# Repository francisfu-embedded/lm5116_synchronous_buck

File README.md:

# lm5116_synchronous_buck
a 72W synchronous buck converter based on TI LM5116

- Features:
Input voltage range from 15 - 50V
Output Voltage: 12V    +- 2.5%
Output Current: Max 6A. Shuts off after reaching the limit
Max efficiency 96% at full load

- Notes:
The inductor of this buck converter circuit is changed from a 22u vishay smd inductor to a 97u toroidal inductor due to excessive inductor heating at no load.
The suspected reason is the inductor current spiking at light load DCM. 
Replacing with higher inductance solves the issue in the design as it decreases the output load "boundary" to CCM
Further investigations on this behaviour still needed!

- Remaining issues:
1. The current design has bad "acoustics". Inductor buzzing is audible. It is normal to have a buzzing noise in a switching converter prototype but it's still not
desirable. Further investigations needed on how to reduce this audible noise in a mature product.

2. After loading the converter and then returning back to no load, the buck converter still draws around 2.1W standby power - which is not seen when the circuit is first
powered up. Further inverstigations needed on this high standby power. It may have to do with the ic itself not in "standby" mode and / or the inductor current spiking
at no load

- Potential applications:
This project is a prototype design using TI's LM5116 and may open up more design ideas involving this chip. For instance, a fan driver or an AA battery charger.
The feedback voltage can be made programmable easily by attaching a filtered-pwm / DAC / pull-down resistors to the feedback pin, thus enabling voltage programming
or even current regulation using an external control loop (e.g. using an MCU). This control scheme is suitable for chargers and variable power supply. Related project 
maybe added to the github in the future.

- Thanks:
Big shout-outs to TI's engineers for their great documentation of the IC and their reference designs

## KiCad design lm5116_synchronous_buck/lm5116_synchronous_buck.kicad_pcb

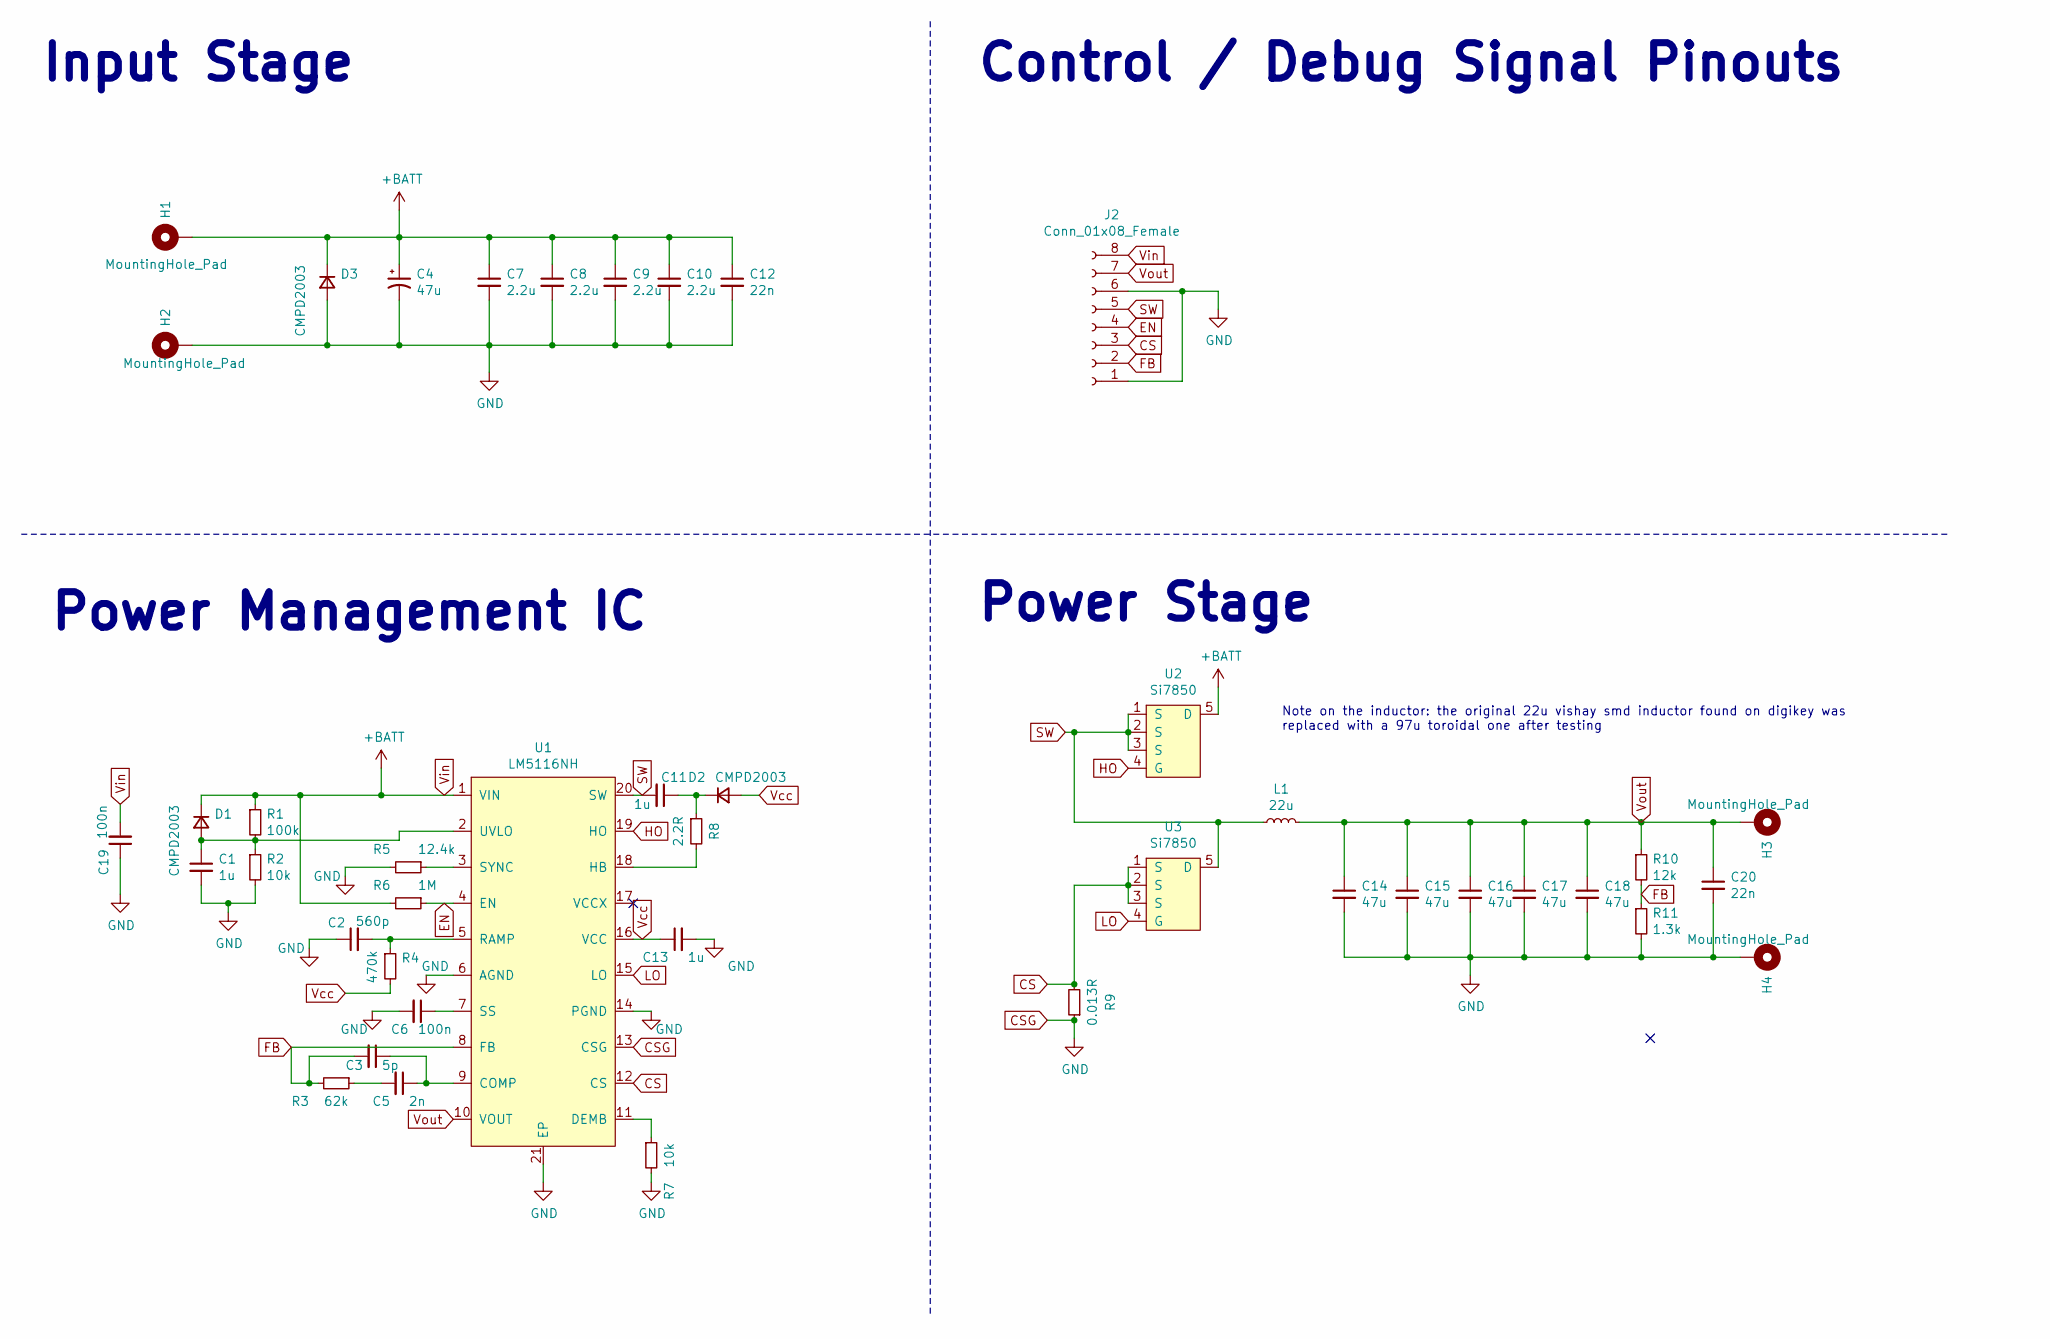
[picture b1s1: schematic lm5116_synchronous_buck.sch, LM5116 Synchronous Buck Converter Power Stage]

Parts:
C1, C11, C13: 1u; C_0603_1608Metric; LCSC Part # C90540
C2: 560p; C_0603_1608Metric; LCSC Part # C1627
C3: 5p; C_0603_1608Metric; LCSC Part # C1669
C4: 47u; C_Elec_8x10.2; LCSC Part # C336483
C5: 2n; C_0603_1608Metric; LCSC Part # C1604
C6, C19: 100n; C_0603_1608Metric; LCSC Part # C83054
C7, C8, C9, C10: 2.2u; C_1206_3216Metric; LCSC Part # C39619
C12, C20: 22n; C_0603_1608Metric; LCSC Part # C1697
C14, C15, C16, C17, C18: 47u; C_1206_3216Metric; LCSC Part # C30300
D1, D2, D3: CMPD2003; D_SOT-23_ANK
H1, H2, H3, H4: MountingHole_Pad; MountingHole_4.5mm_Pad_Via
J2: Conn_01x08_Female; PinHeader_1x08_P2.54mm_Vertical
L1: 22u; L_12x12mm_H6mm
R1: 100k; R_0603_1608Metric; LCSC Part # C25803
R2, R7: 10k; R_0603_1608Metric; LCSC Part # C269701
R3: 62k; R_0603_1608Metric; LCSC Part # C23221
R4: 470k; R_0603_1608Metric; LCSC Part # C25599
R5: 12.4k; R_0603_1608Metric; LCSC Part # C22865
R6: 1M; R_0603_1608Metric; LCSC Part # C22935
R8: 2.2R; R_0805_2012Metric
R9: 0.013R; R_1206_3216Metric; LCSC Part # C201279
R10: 12k; R_0603_1608Metric; LCSC Part # C269442
R11: 1.3k; R_0603_1608Metric; LCSC Part # C22767
U1: LM5116NH; HTSSOP-20-1EP_4.4x6.5mm_P0.65mm_EP3.4x6.5mm; LCSC Part # C13755
U2, U3: Si7850; PowerPAK_SO-8_Single

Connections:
CS: J2.3, R9.2, U1.12 (CS), U3.1 (S), U3.2 (S), U3.3 (S)
CSG: C1.2, C2.1, C4.2, C6.2, C7.2, C8.2, C9.2, C10.2, C12.2, C13.2, C14.2, C15.2, C16.2, C17.2, C18.2, C19.1, C20.2, D3.2 (A), H2.1, H4.1, J2.1, J2.6, R2.2, R5.2, R7.2, R9.1, R11.2, U1.6 (AGND), U1.13 (CSG), U1.14 (PGND), U1.21 (EP)
EN: J2.4, R6.1, U1.4 (EN)
FB: C3.2, J2.2, R3.2, R10.2, R11.1, U1.8 (FB)
HO: U1.19 (HO), U2.4 (G)
LO: U1.15 (LO), U3.4 (G)
unnamed: C1.1, D1.2 (A), R1.2, R2.1, U1.2 (UVLO)
unnamed: C2.2, R4.1, U1.5 (RAMP)
unnamed: C3.1, C5.1, U1.9 (COMP)
unnamed: C5.2, R3.1
unnamed: C6.1, U1.7 (SS)
unnamed: C11.1, D2.1 (K), R8.1
unnamed: R5.1, U1.3 (SYNC)
unnamed: R7.1, U1.11 (DEMB)
unnamed: R8.2, U1.18 (HB)
SW: C11.2, J2.5, L1.1, U1.20 (SW), U2.1 (S), U2.2 (S), U2.3 (S), U3.5 (D)
Vcc: C13.1, D2.2 (A), R4.2, U1.16 (VCC)
Vin: C4.1, C7.1, C8.1, C9.1, C10.1, C12.1, C19.2, D1.1 (K), D3.1 (K), H1.1, J2.8, R1.1, R6.2, U1.1 (VIN), U2.5 (D)
Vout: C14.1, C15.1, C16.1, C17.1, C18.1, C20.1, H3.1, J2.7, L1.2, R10.1, U1.10 (VOUT)

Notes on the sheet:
Input Stage
Control / Debug Signal Pinouts
Power Stage
Power Management IC
Note on the inductor: the original 22u vishay smd inductor found on digikey was replaced with a 97u toroidal one after testing

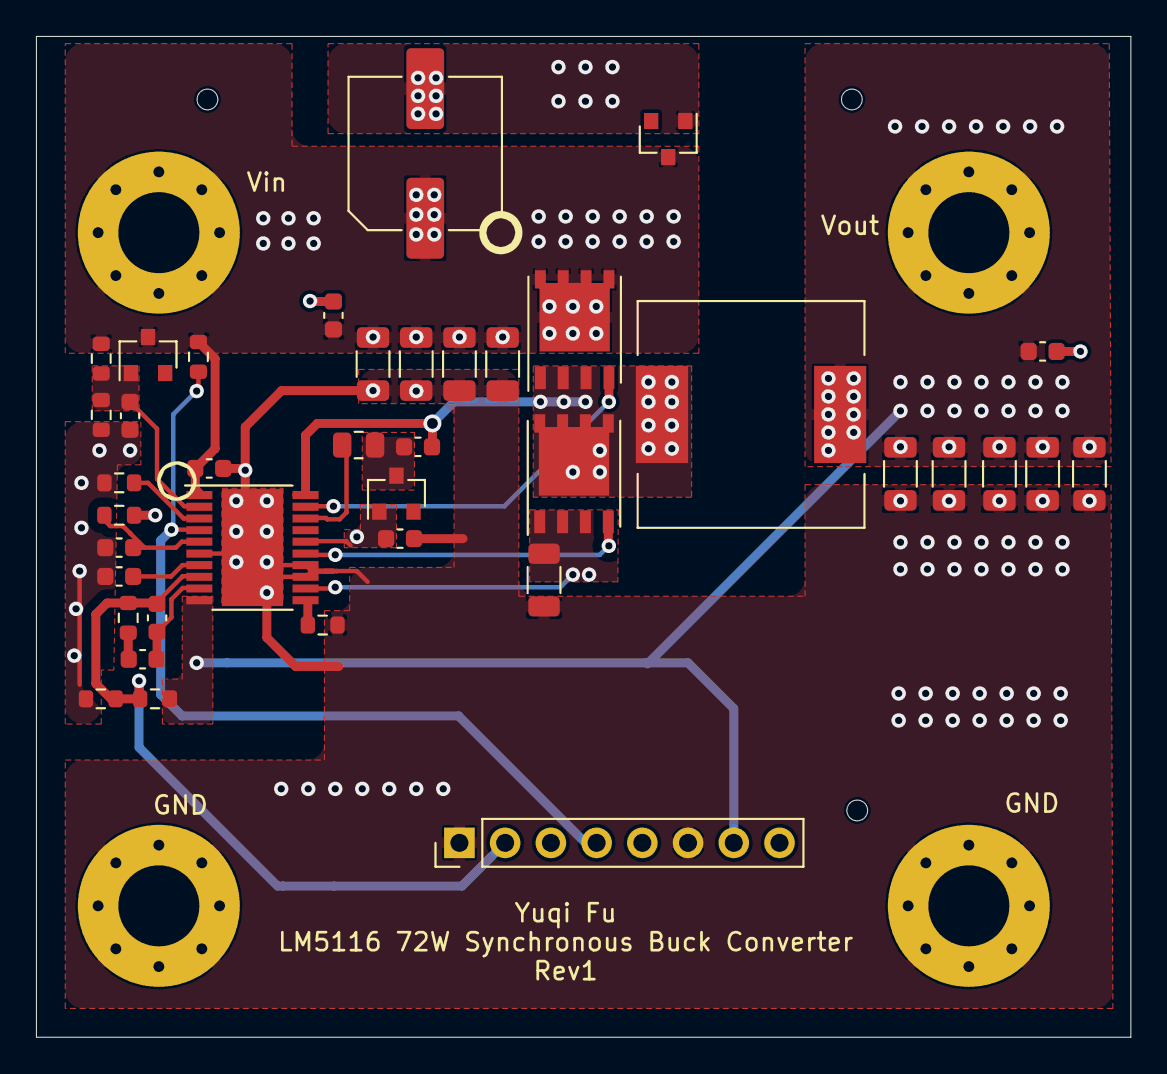
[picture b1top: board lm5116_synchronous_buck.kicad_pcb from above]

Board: 4 copper layers, 60.8 x 55.6 mm, 43 parts (0 on the bottom side), 19 nets.

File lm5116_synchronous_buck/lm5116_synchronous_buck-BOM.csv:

Comment,Designator,Footprint,LCSC
"1u","C1,C11,C13","Capacitor_SMD:C_0603_1608Metric",""
"47u","C14,C15,C16,C17,C18","Capacitor_SMD:C_1206_3216Metric",""
"560p","C2","Capacitor_SMD:C_0603_1608Metric",""
"22n","C12,C20","Capacitor_SMD:C_0603_1608Metric",""
"5p","C3","Capacitor_SMD:C_0603_1608Metric",""
"47u","C4","Capacitor_SMD:C_Elec_8x10.2",""
"2n","C5","Capacitor_SMD:C_0603_1608Metric",""
"100n","C6,C19","Capacitor_SMD:C_0603_1608Metric",""
"2.2u","C7,C8,C9,C10","Capacitor_SMD:C_1206_3216Metric",""
"CMPD2003","D1,D2,D3","Diode_SMD:D_SOT-23_ANK",""
"MountingHole_Pad","H1,H2,H3,H4","MountingHole:MountingHole_4.5mm_Pad_Via",""
"Conn_01x08_Female","J2","Connector_PinHeader_2.54mm:PinHeader_1x08_P2.54mm_Vertical",""
"22u","L1","Inductor_SMD:L_12x12mm_H6mm",""
"100k","R1","Resistor_SMD:R_0603_1608Metric",""
"12k","R10","Resistor_SMD:R_0603_1608Metric",""
"1.3k","R11","Resistor_SMD:R_0603_1608Metric",""
"10k","R2,R7","Resistor_SMD:R_0603_1608Metric",""
"62k","R3","Resistor_SMD:R_0603_1608Metric",""
"470k","R4","Resistor_SMD:R_0603_1608Metric",""
"12.4k","R5","Resistor_SMD:R_0603_1608Metric",""
"1M","R6","Resistor_SMD:R_0603_1608Metric",""
"2.2R","R8","Resistor_SMD:R_0805_2012Metric",""
"0.013R","R9","Resistor_SMD:R_1206_3216Metric",""
"LM5116NH","U1","Package_SO:HTSSOP-20-1EP_4.4x6.5mm_P0.65mm_EP3.4x6.5mm",""
"Si7850","U2,U3","Package_SO:PowerPAK_SO-8_Single",""
